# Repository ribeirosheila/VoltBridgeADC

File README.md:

# VoltBridgeADC ⚡
VoltBridgeADC é um projeto open source que combina eletrônica, programação e design de interface para a criação de um sistema de aquisição de sinais de tensão. Este projeto foi desenvolvido como uma solução simples e prática, ideal para quem deseja aprender ou construir uma base para seu Trabalho de Conclusão de Curso (TCC). O VoltBridgeADC foi projetado para ser adaptável, permitindo que outros desenvolvedores expandam suas funcionalidades ou ajustem o sistema conforme suas necessidades.

Este foi o meu primeiro projeto de PCB e também o meu primeiro trabalho utilizando microcontroladores da STMicroelectronics, uma experiência que me permitiu explorar desde a programação em baixo nível até o desenvolvimento de hardware.

## Sobre o Projeto 🚀
O VoltBridgeADC foi desenvolvido utilizando:

## Microcontrolador
O sistema é baseado no STM32L053R8T6, que oferece baixo consumo de energia e é ideal para aplicações de aquisição de sinais. Toda a programação do microcontrolador foi feita em C, utilizando o STM32CubeIDE, com foco na simplicidade e eficiência para gerenciar a comunicação e a leitura de tensões.

## Interface com o Usuário 💻
A interface foi implementada no LabVIEW, empregando o design pattern Produtor-Consumidor para separar o envio de comandos do processamento dos dados recebidos. O produtor envia comandos de "Start", "Pause" e "Stop", enquanto o consumidor gerencia a comunicação com o microcontrolador e apresenta as leituras de tensão. Apesar de ser simples, a interface é funcional e intuitiva, oferecendo recursos como:

- Seleção da porta USB do microcontrolador.
- Controle da comunicação com botões dedicados.
- Visualização em tempo real da tensão lida.

Este foi o meu primeiro projeto no LabVIEW, e ele foi uma oportunidade de explorar a integração entre software e hardware.

## Desenvolvimento de PCB 🛠️
A placa do VoltBridgeADC foi projetada no KiCad, com atenção aos detalhes:

- Material: FR-4, garantindo durabilidade e resistência térmica.
- Acabamento: HASL, para melhorar a soldabilidade e reduzir custos.
- Organização lógica dos componentes para facilitar o roteamento.
- Trilhas com ângulos de 45°, priorizando integridade elétrica e redução de ruídos.
- Uso de furos para fixação mecânica, que também servem como pontos de aterramento (GND).
- Dimensões compactas: 68 mm x 99 mm, com bordas arredondadas para um design refinado.
- Os arquivos Gerber para a fabricação da PCB estão disponíveis no repositório, permitindo que qualquer pessoa possa produzir sua própria placa com facilidade.

## Sugestões para Melhorias ✨
Este projeto foi projetado para ser um ponto de partida, e há diversas possibilidades de melhorias:

- Substituição do Microcontrolador: Desenvolvedores podem optar pelo Arduino ou outros microcontroladores mais acessíveis, ajustando o código e o circuito para compatibilidade.
- Melhorias na Interface de Usuário: A interface em LabVIEW pode ser substituída ou aprimorada, utilizando outras linguagens de programação, como Python ou C#, para maior flexibilidade e recursos adicionais.
- Atualização da PCB: Melhorias no layout da placa, otimização do circuito e inclusão de novos recursos podem ser feitas.
- Aprimoramento do Código em C: Refatoração e adição de funcionalidades ao código do microcontrolador para torná-lo mais robusto e versátil.
- Substituição da comunicação serial UART por Bluetooth ou Wi-Fi: Implementar comunicação via Bluetooth ou Wi-Fi pode modernizar o projeto, facilitando a transmissão de dados do microcontrolador para a interface de usuário. Isso também permitiria o acompanhamento da tensão em tempo real diretamente pelo celular do usuário, ao invés de somente pelo PC, oferecendo mais praticidade e conectividade ao sistema.

## Licença 🆓
O VoltBridgeADC é um projeto open source, desenvolvido com o objetivo de compartilhar conhecimento e auxiliar outros entusiastas e estudantes. Sinta-se à vontade para usá-lo em seus próprios projetos ou como base para o seu TCC. Contribuições e melhorias são sempre bem-vindas!

Acesse o projeto, explore os arquivos disponíveis, e contribua com sugestões ou adaptações! 📈

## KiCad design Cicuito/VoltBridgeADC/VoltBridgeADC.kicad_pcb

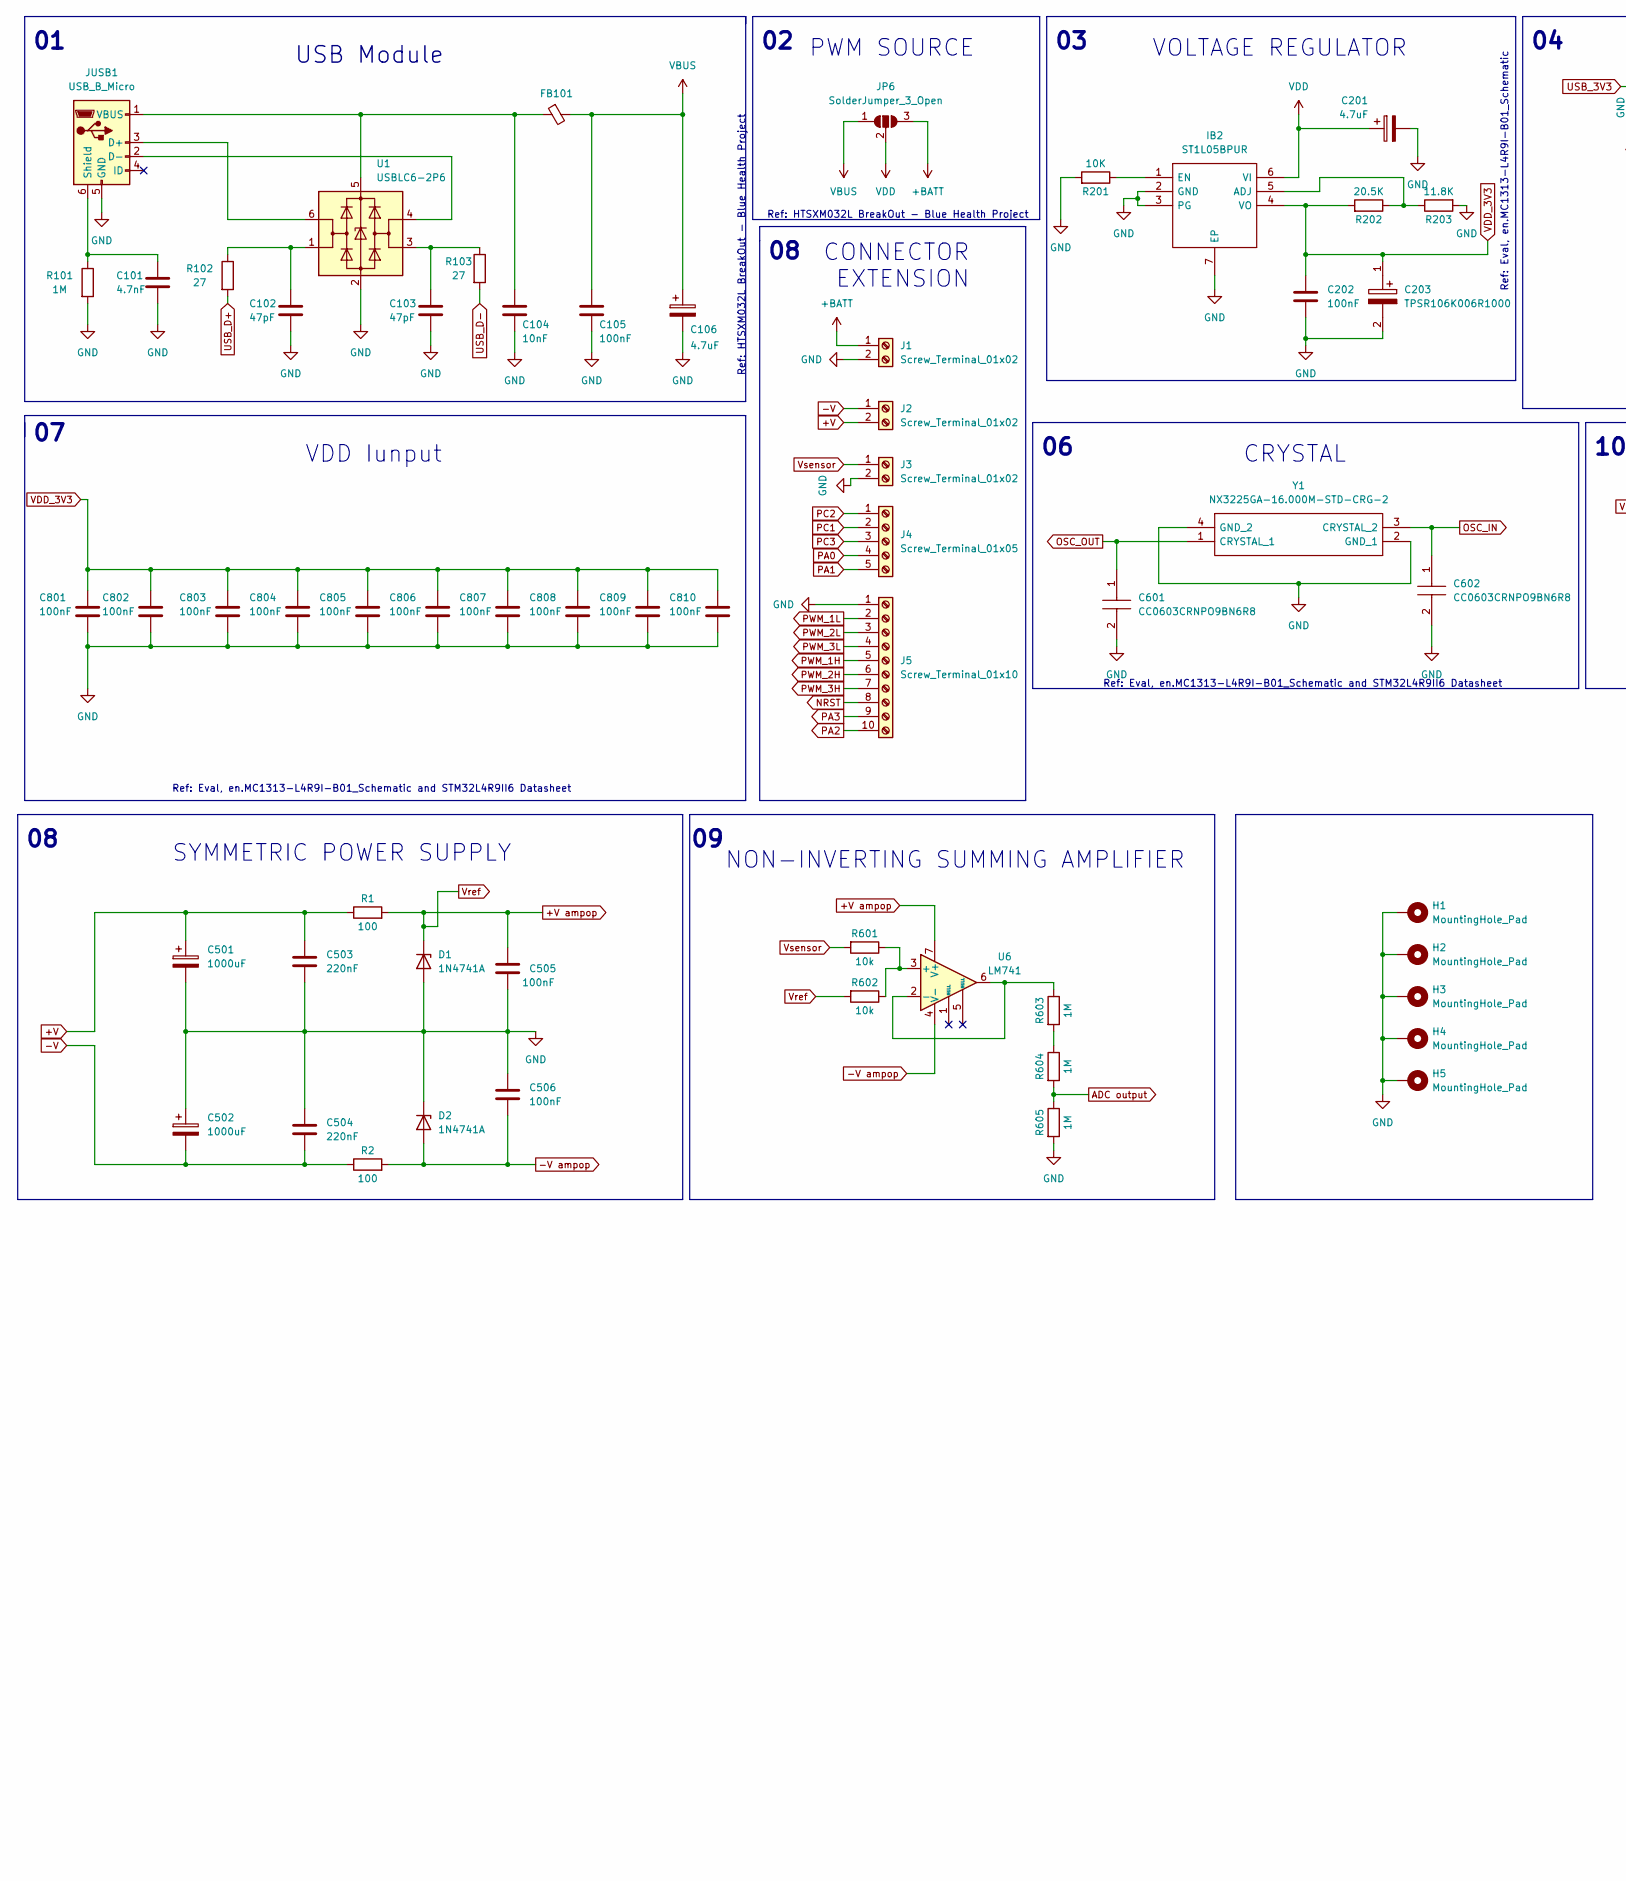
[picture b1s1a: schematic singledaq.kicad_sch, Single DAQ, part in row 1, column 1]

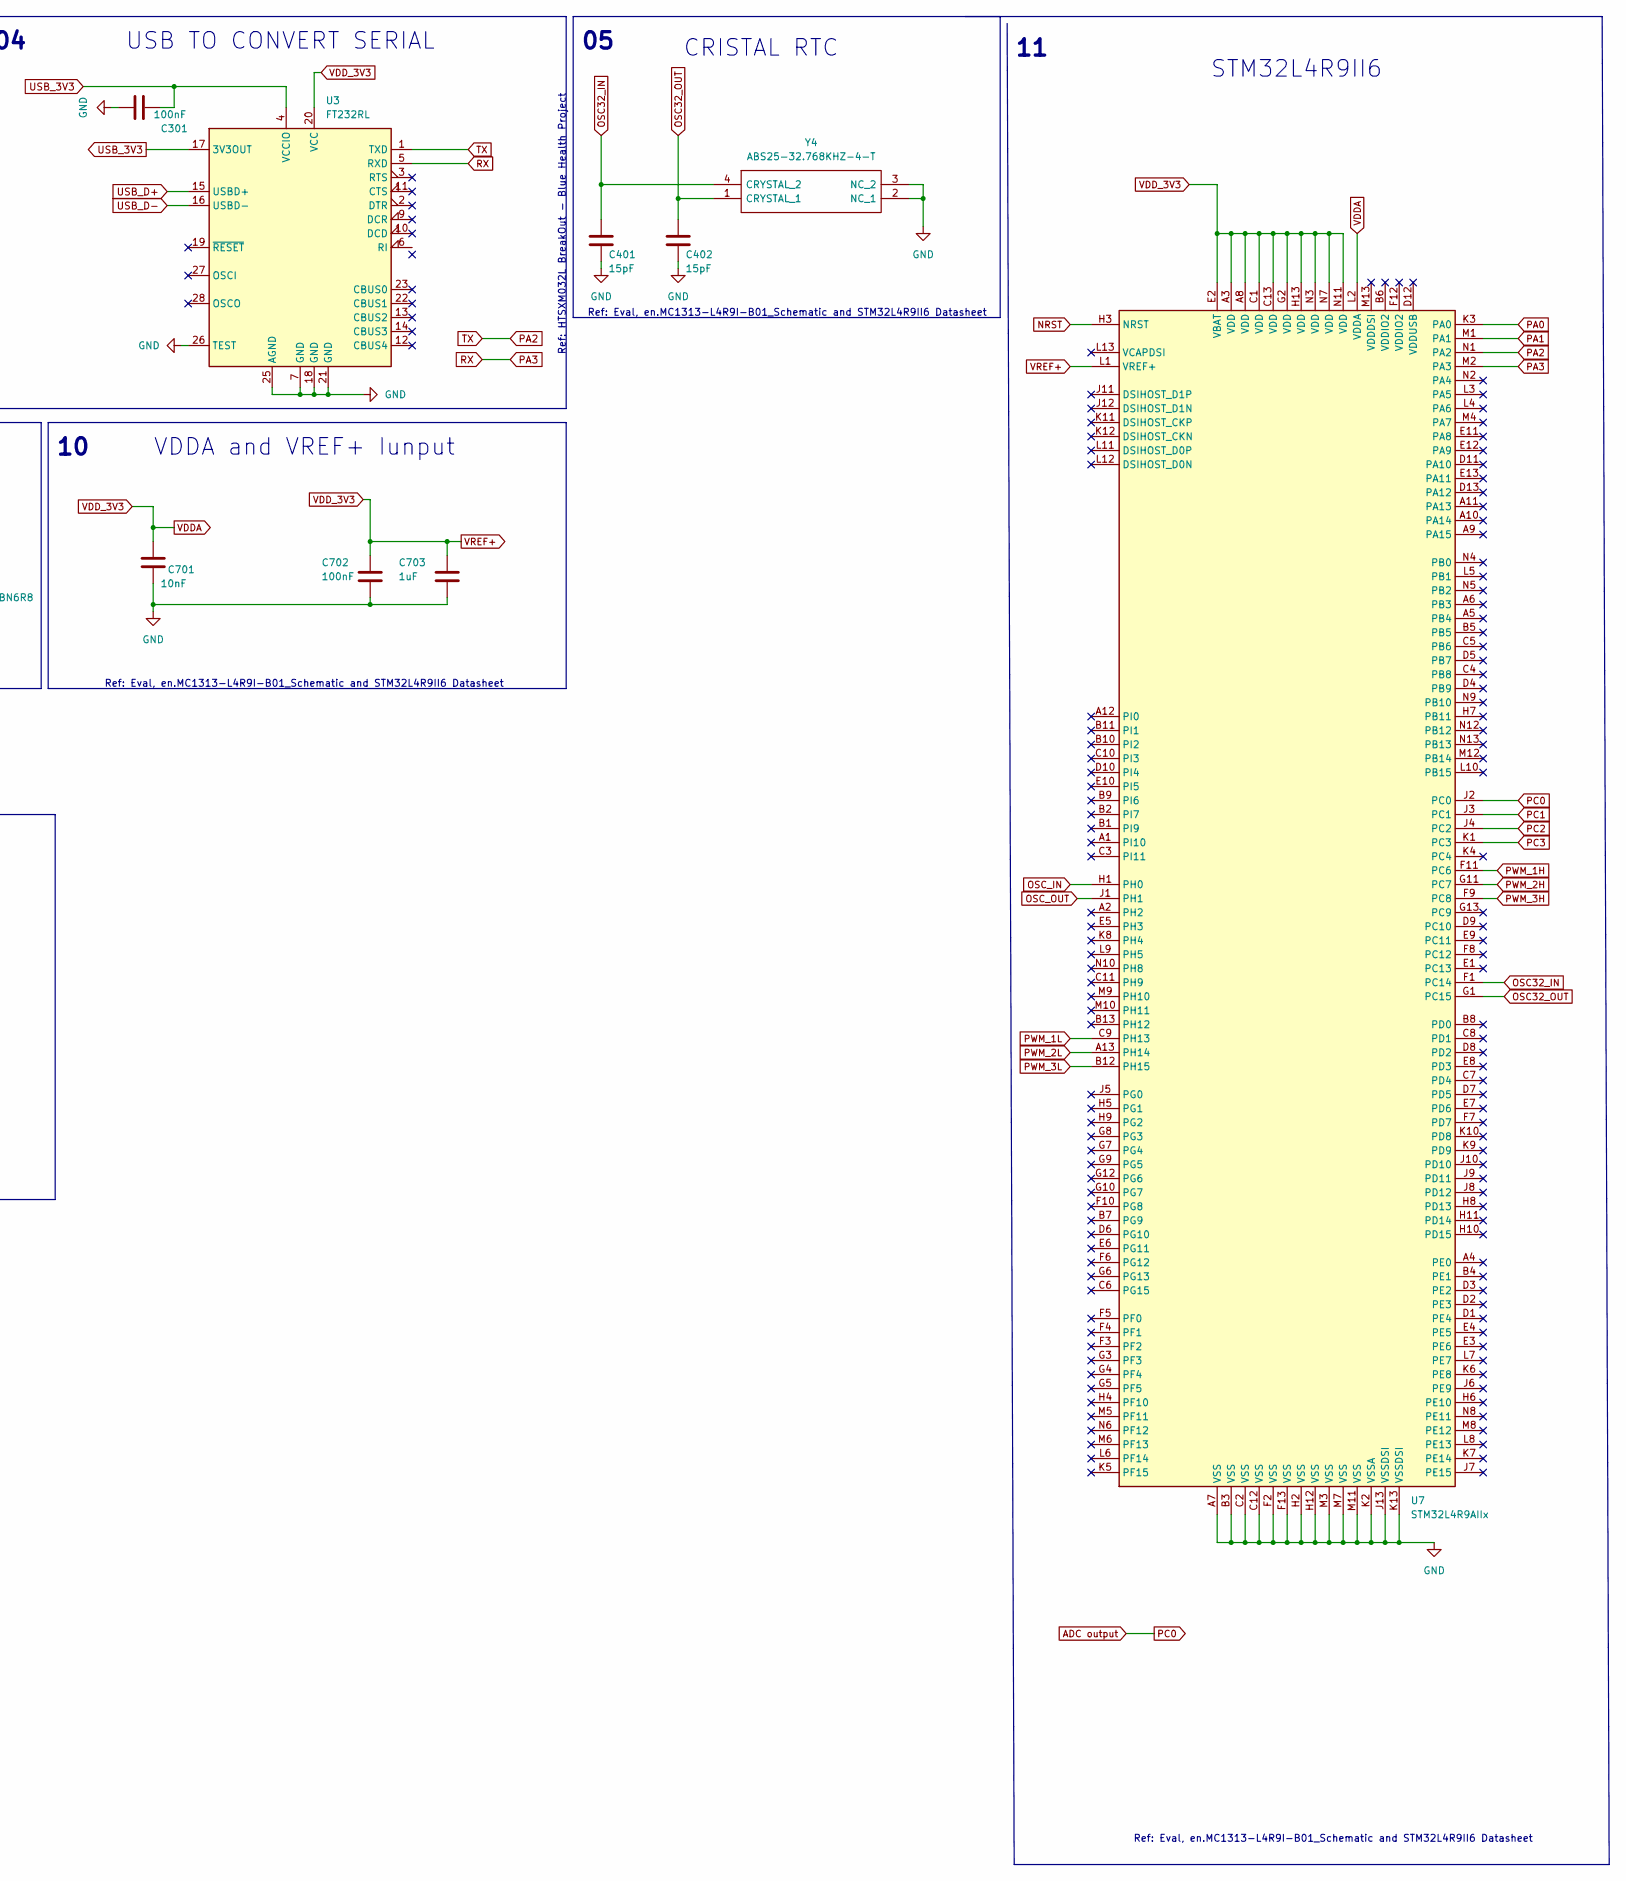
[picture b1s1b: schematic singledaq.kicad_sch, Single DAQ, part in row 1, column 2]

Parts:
C101: 4.7nF; C_0805_2012Metric
C102, C103: 47pF; C_0805_2012Metric
C104, C701: 10nF; C_0805_2012Metric
C105, C202, C301, C702, C801, C802, C803, C804, C805, C806, C807, C808, C809, C810: 100nF; C_0805_2012Metric
C106, C201: 4.7uF; CP_Elec_4x5.4
C203: TPSR106K006R1000; CAPC2012X140N; Manufacturer_Part_Number TPSR106K006R1000; Mouser Part Number 581-TPSR106K006R1000
C401, C402: 15pF; C_0805_2012Metric
C501, C502: 1000uF; CP_Radial_D13.0mm_P5.00mm
C503, C504: 220nF; C_0603_1608Metric_Pad1.08x0.95mm_HandSolder
C505, C506: 100nF; C_1206_3216Metric
C601, C602: CC0603CRNPO9BN6R8; CAPC1608X90; Manufacturer_Part_Number CC0603CRNPO9BN6R8; Mouser Part Number 603-CC603CRNPO9BN6R8
C703: 1uF; C_0805_2012Metric
D1, D2: 1N4741A; D_DO-41_SOD81_P10.16mm_Horizontal
FB101: FerriteBead_Small; R_0805_2012Metric
H1, H2, H3, H4, H5: MountingHole_Pad; MountingHole_4.3mm_M4_Pad_Via
IB2: ST1L05BPUR; SON95P300X300X100-7N; Manufacturer_Part_Number ST1L05BPUR; Mouser Part Number 511-ST1L05BPUR
J1, J2, J3: Screw_Terminal_01x02; TerminalBlock_Altech_AK300-2_P5.00mm
J4: Screw_Terminal_01x05; TerminalBlock_4Ucon_1x05_P3.50mm_Horizontal
J5: Screw_Terminal_01x10; TerminalBlock_4Ucon_1x10_P3.50mm_Horizontal
JP6: SolderJumper_3_Open; PinHeader_1x03_P2.54mm_Vertical
JUSB1: USB_B_Micro; USB_Micro-B_Amphenol_10103594-0001LF_Horizontal
R1, R2: 100; R_2816_7142Metric_Pad3.20x4.45mm_HandSolder
R101, R603, R604, R605: 1M; R_2512_6332Metric_Pad1.40x3.35mm_HandSolder
R102, R103: 27; R_2512_6332Metric_Pad1.40x3.35mm_HandSolder
R201: 10K; R_2512_6332Metric_Pad1.40x3.35mm_HandSolder
R202: 20.5K; R_2512_6332Metric_Pad1.40x3.35mm_HandSolder
R203: 11.8K; R_2512_6332Metric_Pad1.40x3.35mm_HandSolder
R601, R602: 10k; R_2512_6332Metric_Pad1.40x3.35mm_HandSolder
U1: USBLC6-2P6; SOT-23-6
U3: FT232RL; SSOP-28_5.3x10.2mm_P0.65mm
U6: LM741; DIP-8_W7.62mm
U7: STM32L4R9AIIx; UFBGA-169_7x7mm_Layout13x13_P0.5mm
Y1: NX3225GA-16.000M-STD-CRG-2; OSCCC320X250X90N; Manufacturer_Part_Number NX3225GA-16.000M-STD-CRG-2
Y4: ABS25-32.768KHZ-4-T; XTAL_ABS25-32.768KHZ-4-T; Manufacturer_Part_Number ABS25-32.768KHZ-4-T; Mouser Part Number 815-ABS25-32.7K-4-T

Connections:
+BATT: J1.1, JP6.3 (B)
+V: C501.1, C503.1, J2.2, R1.1
+V ampop: C505.1, D1.1 (K), R1.2, R602.2, U6.7 (V+)
-V: C502.2, C504.2, J2.1, R2.1
-V ampop: C506.2, D2.2 (A), R2.2, U6.4 (V-)
ADC output: R604.2, R605.1, U7.J2 (PC0)
GND: C101.2, C102.2, C103.2, C104.2, C105.2, C106.2, C201.2, C202.2, C203.2, C301.2, C401.2, C402.2, C501.2, C502.1, C503.2, C504.1, C505.2, C506.1, C601.2, C602.2, C701.2, C702.2, C703.2, C801.2, C802.2, C803.2, C804.2, C805.2, C806.2, C807.2, C808.2, C809.2, C810.2, D1.2 (A), D2.1 (K), H1.1, H2.1, H3.1, H4.1, H5.1, IB2.2 (GND), IB2.3 (PG), IB2.7 (EP), J1.2, J3.2, J5.1, JUSB1.5 (GND), R101.2, R201.2, R203.2, R605.2, U1.2 (GND), U3.7 (GND), U3.18 (GND), U3.21 (GND), U3.25 (AGND), U3.26 (TEST), U7.A7 (VSS), U7.B3 (VSS), U7.C2 (VSS), U7.C12 (VSS), U7.F2 (VSS), U7.F13 (VSS), U7.H2 (VSS), U7.H12 (VSS), U7.J13 (VSSDSI), U7.K2 (VSSA), U7.K13 (VSSDSI), U7.M3 (VSS), U7.M7 (VSS), U7.M11 (VSS), Y1.2 (GND_1), Y1.4 (GND_2), Y4.2 (NC_1), Y4.3 (NC_2)
NRST: J5.8, U7.H3 (NRST)
unnamed: C101.1, JUSB1.6 (Shield), R101.1
unnamed: C102.1, R102.1, U1.1 (I/O1)
unnamed: C103.1, R103.1, U1.3 (I/O2)
unnamed: C104.1, FB101.1, JUSB1.1 (VBUS), U1.5 (VBUS)
unnamed: IB2.1 (EN), R201.1
unnamed: IB2.5 (ADJ), R202.1, R203.1
unnamed: JUSB1.2 (D-), U1.4 (I/O2)
unnamed: JUSB1.3 (D+), U1.6 (I/O1)
unnamed: R601.1, R602.1, U6.3 (+)
unnamed: R603.1, U6.2 (-), U6.6
unnamed: R603.2, R604.1
OSC32_IN: C401.1, U7.F1 (PC14), Y4.4 (CRYSTAL_2)
OSC32_OUT: C402.1, U7.G1 (PC15), Y4.1 (CRYSTAL_1)
OSC_IN: C602.1, U7.H1 (PH0), Y1.3 (CRYSTAL_2)
OSC_OUT: C601.1, U7.J1 (PH1), Y1.1 (CRYSTAL_1)
PA0: J4.4, U7.K3 (PA0)
PA1: J4.5, U7.M1 (PA1)
PA2: J5.10, U3.1 (TXD), U7.N1 (PA2)
PA3: J5.9, U3.5 (RXD), U7.M2 (PA3)
PC1: J4.2, U7.J3 (PC1)
PC2: J4.1, U7.J4 (PC2)
PC3: J4.3, U7.K1 (PC3)
PWM_1H: J5.5, U7.F11 (PC6)
PWM_1L: J5.2, U7.C9 (PH13)
PWM_2H: J5.6, U7.G11 (PC7)
PWM_2L: J5.3, U7.A13 (PH14)
PWM_3H: J5.7, U7.F9 (PC8)
PWM_3L: J5.4, U7.B12 (PH15)
USB_3V3: C301.1, U3.4 (VCCIO), U3.17 (3V3OUT)
USB_D+: R102.2, U3.15 (USBD+)
USB_D-: R103.2, U3.16 (USBD-)
VBUS: C105.1, C106.1, FB101.2, JP6.1 (A)
VDD: C201.1, IB2.6 (VI), JP6.2 (C)
VDDA: C202.1, C203.1, C701.1, C702.1, C703.1, C801.1, C802.1, C803.1, C804.1, C805.1, C806.1, C807.1, C808.1, C809.1, C810.1, IB2.4 (VO), R202.2, U3.20 (VCC), U7.A3 (VDD), U7.A8 (VDD), U7.C1 (VDD), U7.C13 (VDD), U7.E2 (VBAT), U7.G2 (VDD), U7.H13 (VDD), U7.L1 (VREF+), U7.L2 (VDDA), U7.N3 (VDD), U7.N7 (VDD), U7.N11 (VDD)
Vsensor: J3.1, R601.2

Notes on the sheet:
Ref: Eval, en.MC1313-L4R9I-B01_Schematic and STM32L4R9II6 Datasheet
USB TO CONVERT SERIAL
STM32L4R9II6
VDDA and VREF+ Iunput
PWM SOURCE
CRISTAL RTC
Ref: HTSXM032L BreakOut - Blue Health Project
Ref: Eval, en.MC1313-L4R9I-B01_Schematic
CRYSTAL
CONNECTOR EXTENSION
VOLTAGE REGULATOR
USB Module
NON-INVERTING SUMMING AMPLIFIER
SYMMETRIC POWER SUPPLY
VDD Iunput

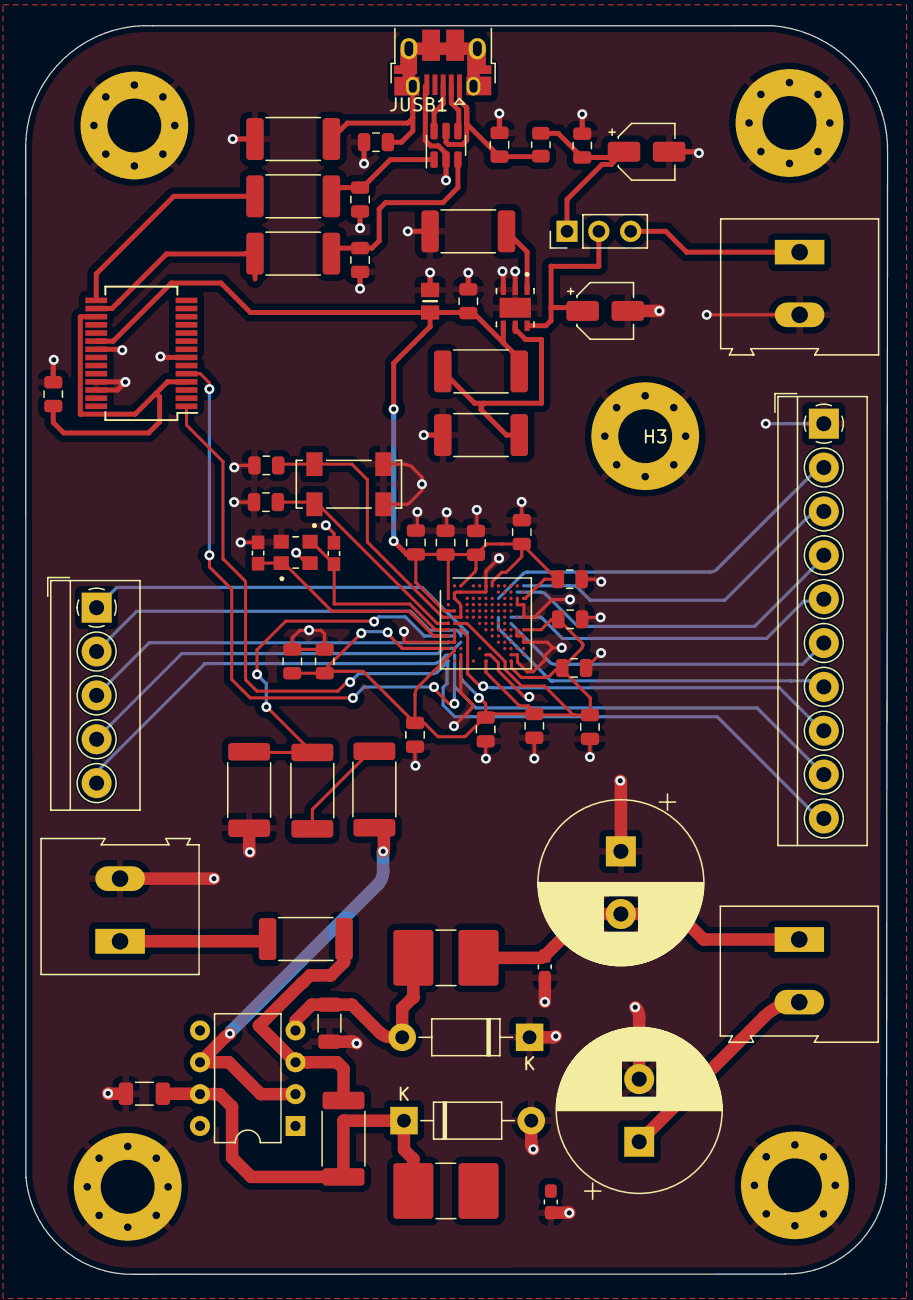
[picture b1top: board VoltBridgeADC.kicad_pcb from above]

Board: 2 copper layers, 68.8 x 99.6 mm, 68 parts (0 on the bottom side), 43 nets.

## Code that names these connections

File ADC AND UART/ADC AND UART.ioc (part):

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Mcu.Name=STM32L053R(6-8)Tx
Mcu.Package=LQFP64
Mcu.UserName=STM32L053R8Tx
PA0.Mode=IN0
PA0.Signal=ADC_IN0
PA2.Mode=Multiprocessor_communication
PA2.Signal=USART2_TX
PA3.Mode=Multiprocessor_communication
PA3.Signal=USART2_RX
PH0-OSC_IN.Mode=HSE-External-Oscillator
PH0-OSC_IN.Signal=RCC_OSC_IN
PH1-OSC_OUT.Mode=HSE-External-Oscillator
PH1-OSC_OUT.Signal=RCC_OSC_OUT
RCC.HSE_VALUE=8000000
RCC.SYSCLKFreq_VALUE=2097000
board=custom

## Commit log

2024-11-21 Create VoltBridgeADC
    First uptade
2024-11-21 Uptade File
2024-11-21 Organização dos arquivo e alteração do documento sobre o projeto
    Foram incluídas no documento sobre o projeto informações sobre a PCB. As pastas do projeto também foram organizadas corretamente.
2024-11-21 Inclusão das imagens do código do LabView
2024-11-21 Atualização da documentação
    Atualização do documento com as informações e detalhes sobre o código do labview
2024-11-21 Update Documentação
    Inclusão da imagem e informação de que foi utilizada uma placa da ST
2024-11-21 Inclusão de imagens
    Inclusão das imagens reais
2024-11-21 Deletado arquivo
2024-11-21 Atualizar o README.md
